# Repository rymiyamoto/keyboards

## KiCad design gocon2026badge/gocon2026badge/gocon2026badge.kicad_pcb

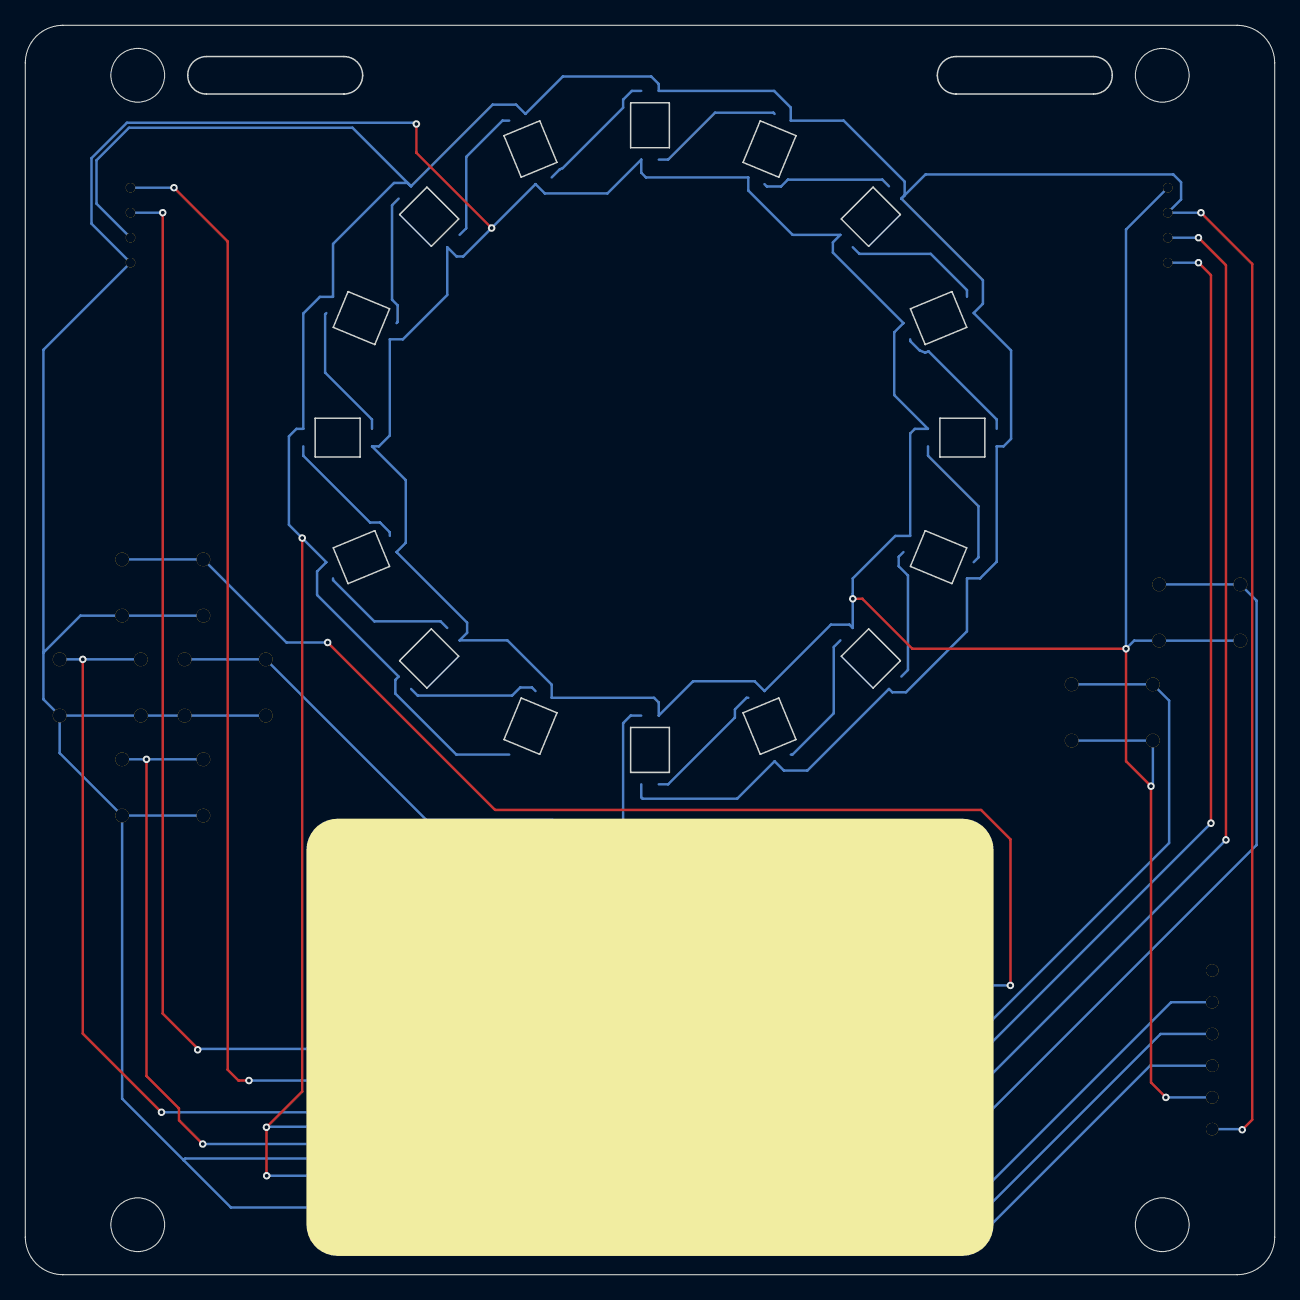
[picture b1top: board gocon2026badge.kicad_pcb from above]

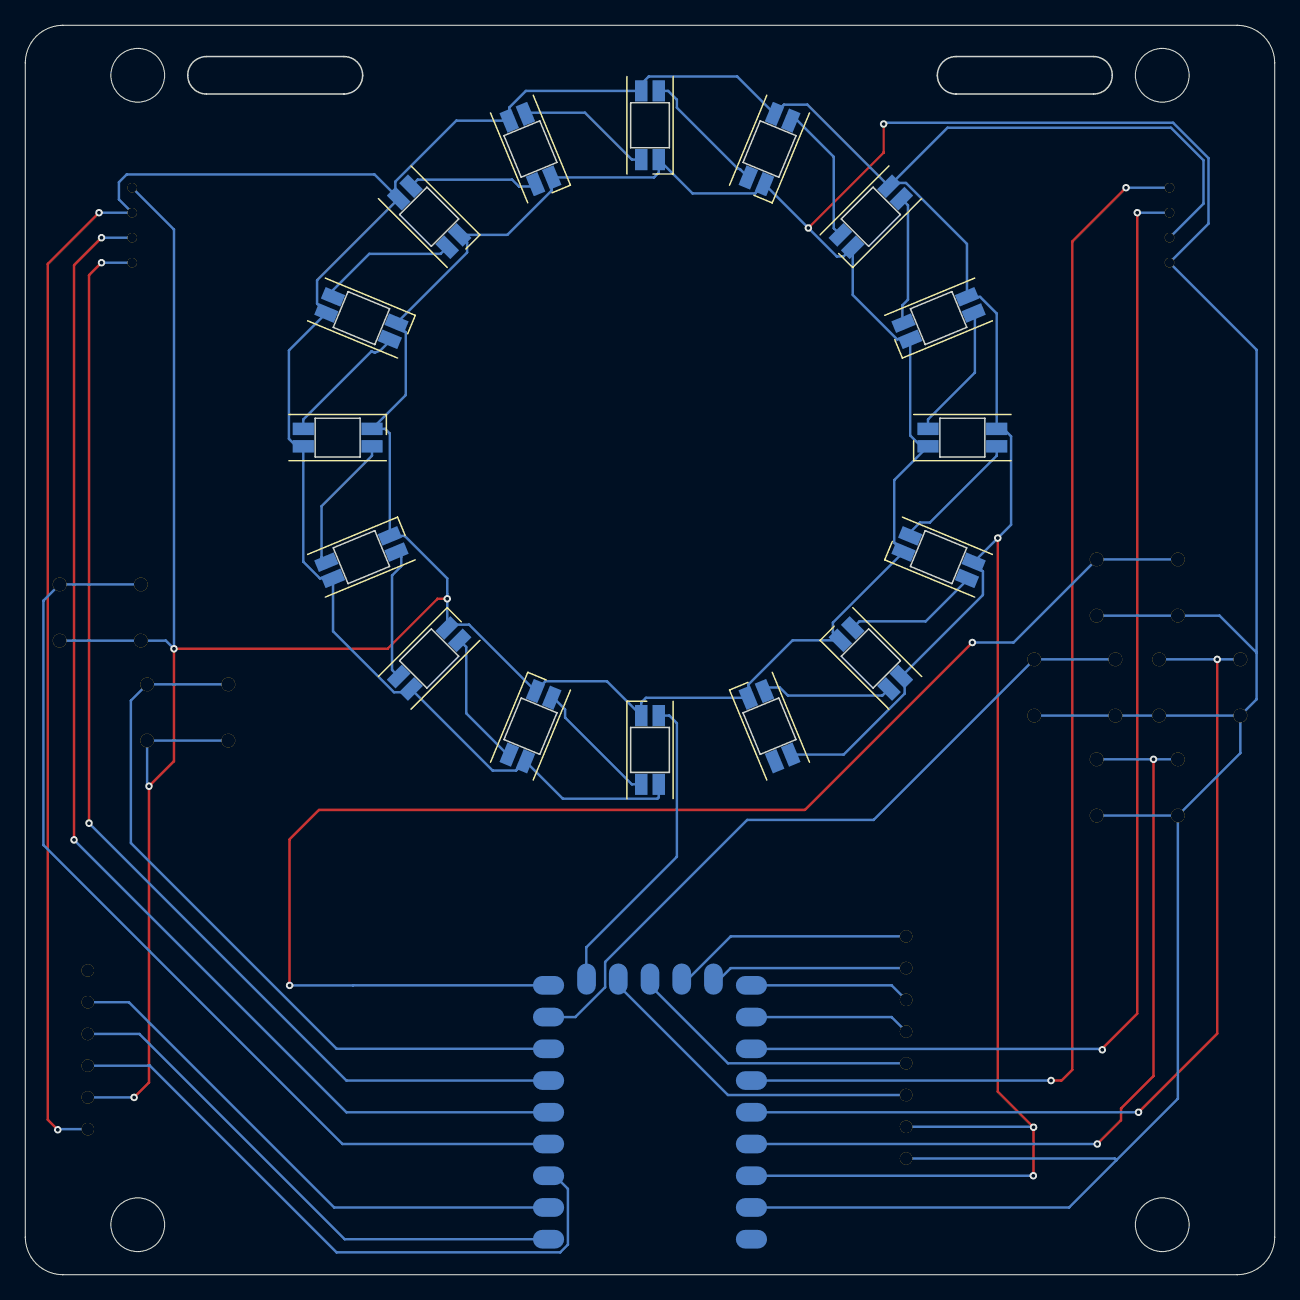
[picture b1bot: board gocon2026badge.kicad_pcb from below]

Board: 2 copper layers, 100.0 x 100.0 mm, 33 parts (17 on the bottom side), 37 nets.

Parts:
LED1, LED2, LED3, LED4, LED5, LED6, LED7, LED8, LED9, LED10, LED11, LED12, LED13, LED14, LED15, LED16: YS-SK6812MINI-E
SW1, SW2, SW3, SW4, SW5, SW6: SW_PUSH; SW_PUSH_6mm_H5mm-b
U1: rp2040-zero; rp2040-zero-smd
U2: ST7789-1.54TFT-SPI; ST7789-1.54TFT-SPI-b
U3, U5: GROVE_I2C_UART; grove-horizontal-b
U4: PCM510x; PinHeader_1x06_P2.54mm_Vertical-b
U91, U92, U93, U94: (no value)
hole1, hole2: strap_hole

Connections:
BL: U1.13 (12), U2.8 (BL)
BTN_A: SW5.1, U1.4 (3)
BTN_B: SW6.1, U1.7 (6)
BTN_DOWN: SW3.1, U1.20 (29)
BTN_LEFT: SW2.1, U1.19 (28)
BTN_RIGHT: SW4.1, U1.8 (7)
BTN_UP: SW1.1, U1.9 (8)
CS: U1.14 (13), U2.7 (CS)
DC: U1.15 (14), U2.6 (DC)
GND: LED1.3 (VSS), LED2.3 (VSS), LED3.3 (VSS), LED4.3 (VSS), LED5.3 (VSS), LED6.3 (VSS), LED7.3 (VSS), LED8.3 (VSS), LED9.3 (VSS), LED10.3 (VSS), LED11.3 (VSS), LED12.3 (VSS), LED13.3 (VSS), LED14.3 (VSS), LED15.3 (VSS), LED16.3 (VSS), SW1.2, SW2.2, SW3.2, SW4.2, SW5.2, SW6.2, U1.22 (GND), U2.1 (GND), U3.4 (GND), U4.5 (GND), U5.4 (GND)
I2C0_SCL: U1.6 (5), U3.1 (SCL_RX)
I2C0_SDA: U1.5 (4), U3.2 (SDA_TX)
I2C1_SCL: U1.18 (27), U5.1 (SCL_RX)
I2C1_SDA: U1.17 (26), U5.2 (SDA_TX)
unnamed: LED1.2 (DOUT), LED2.4 (DIN)
unnamed: LED2.2 (DOUT), LED3.4 (DIN)
unnamed: LED3.2 (DOUT), LED4.4 (DIN)
unnamed: LED4.2 (DOUT), LED5.4 (DIN)
unnamed: LED5.2 (DOUT), LED6.4 (DIN)
unnamed: LED6.2 (DOUT), LED7.4 (DIN)
unnamed: LED7.2 (DOUT), LED8.4 (DIN)
unnamed: LED8.2 (DOUT), LED9.4 (DIN)
unnamed: LED9.2 (DOUT), LED10.4 (DIN)
unnamed: LED10.2 (DOUT), LED11.4 (DIN)
unnamed: LED11.2 (DOUT), LED12.4 (DIN)
unnamed: LED12.2 (DOUT), LED13.4 (DIN)
unnamed: LED13.2 (DOUT), LED14.4 (DIN)
unnamed: LED14.2 (DOUT), LED15.4 (DIN)
unnamed: LED15.2 (DOUT), LED16.4 (DIN)
PCM510x_BCK: U1.2 (1), U4.2 (BCK)
PCM510x_DIN: U1.1 (0), U4.3 (DIN)
PCM510x_LRCK: U1.3 (2), U4.4 (LRCK)
RST: U1.16 (15), U2.5 (RST)
SPI_SCK: U1.11 (10), U2.3 (SCL)
SPI_SDO: U1.12 (11), U2.4 (SDA)
VCC: LED1.1 (VDD), LED2.1 (VDD), LED3.1 (VDD), LED4.1 (VDD), LED5.1 (VDD), LED6.1 (VDD), LED7.1 (VDD), LED8.1 (VDD), LED9.1 (VDD), LED10.1 (VDD), LED11.1 (VDD), LED12.1 (VDD), LED13.1 (VDD), LED14.1 (VDD), LED15.1 (VDD), LED16.1 (VDD), U1.21 (3V3), U2.2 (VCC), U3.3 (VCC), U4.6 (VIN), U5.3 (VCC)
WS2812B: LED1.4 (DIN), U1.10 (9)
